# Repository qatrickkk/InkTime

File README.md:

# InkTime Smartwatch

InkTime is a custom, open source smartwatch based on Nordic nRF52840, designed to have a low power consumption. It features an E-Ink display, 3-axis accelerometer, haptic feedback, and a 3 button navigation system.

## System Architecture Diagram
```mermaid
flowchart LR
    subgraph PWR["Power Subsystem"]
        USB["USB-C"]
        CHG["BQ25180<br/>Li-Ion Charger / Power Path"]
        BAT["AKY0106<br/>Li-Po Battery"]
        FG["MAX17048<br/>Fuel Gauge"]
        REG["RT6160<br/>Buck-Boost 3.3 V"]
        EPDPWR["E-Paper Drive Circuit<br/>(boost / gate / HV rails)"]
    end

    subgraph CTRL["Main Control"]
        MCU["nRF52840"]
    end

    subgraph PERI["Peripherals"]
        EPD["WSH-12561<br/>E-Ink Display"]
        IMU["BMA423 IMU"]
        HAPTIC["DRV2605<br/>Haptic Driver"]
        MOTOR["FIT0774<br/>Vibration Motor"]
        BTN["3 Physical Buttons<br/>(UP / ENTER / DOWN)"]
    end

    USB -->|VBUS| CHG
    BAT <-->|VBAT| CHG
    BAT -->|Cell voltage| FG
    CHG -->|SYS / VREG| REG
    REG -->|3V3| MCU
    REG -->|3V3| IMU
    REG -->|3V3| FG
    REG -->|3V3| HAPTIC
    REG -->|3V3| EPDPWR
    EPDPWR -->|EPD_3V3 + PREVGH / PREVGL| EPD

    MCU <-->|I2C| IMU
    MCU <-->|I2C| FG
    MCU <-->|I2C| HAPTIC
    MCU <-->|I2C| CHG
    MCU <-->|I2C| REG

    MCU -->|SPI SCK / MOSI| EPD
    MCU -->|GPIO: CS / DC / RST| EPD
    EPD -->|GPIO: BUSY| MCU

    MCU <-->|GPIO| BTN
    MCU -->|EN / TRIG| HAPTIC
    HAPTIC -->|OUT+ / OUT-| MOTOR
```

## Hardware Functionality
The nRF52840 is the central controller of the InkTime smartwatch. It runs the firmware, decides when to sleep and wake up, reads sensors, updates the display, handles the buttons, and manages communication with the other chips.

Around the MCU, there are five smaller systems that work together to create a fully functional smartwatch.

The power system is responsible for providing clean power used to charge and operate the watch.

- USB-C brings power from the charger,
- BQ25180 charges the battery and manages the power flow,
- AKY0106 is the battery itself,
- RT6160 generates the regulated 3.3 V rail,
- MAX17048 monitors the battery status and indicates how full it is.

The display system is the bridge between the internal data and the actual information the user sees. Unlike LCD or OLED panels, it does not need continuous power to hold an image, because the ink particles remain in the same position. Therefore, power is mainly used only when the image is changed or refreshed, making it well suited for this use case.

The motion system helps the smartwatch stay in a low-power state by using IMU data, allowing the watch to wake up only when a specific motion occurs, for example a tilt.

The haptic system is based on the DRV2605 haptic driver. Its role is to give the smartwatch user physical feedback through vibration, for example when a notification appears, an alarm is triggered, or a button press is confirmed.

The user input system is formed by three physical buttons: SW_UP, SW_ENT, and SW_DW. These buttons allow the user to interact with the smartwatch in a simple and reliable way.

Power Profile Estimate
- the nRF52840 stays in deep sleep most of the time, below 10 µA,
- the watch wakes once per minute,
- the E-Ink display is refreshed for about 1–2 s,
- active current during refresh is around 8–10 mA.

## nRF52840 Pin Allocation
| Peripheral       | Pin(s)        | Function     | Justification                                 |
| ---------------- | ------------- | ------------ | --------------------------------------------- |
| SPI SCK          | P0.02         | Clock        | SPI clock for the E-Ink display.              |
| SPI MOSI         | P0.03         | Data         | Sends pixel data to the E-Ink display.        |
| EPD CS           | P0.05         | Chip Select  | Selects the display on the SPI bus.           |
| I2C SDA          | P0.06         | Data         | Shared data line for sensors and power ICs.   |
| I2C SCL          | P0.07         | Clock        | Shared clock line for the I2C bus.            |
| IMU INT1         | P0.08         | Interrupt    | Main interrupt from the IMU.                  |
| Fuel Gauge ALERT | P0.09         | Interrupt    | Battery alert signal from MAX17048.           |
| PMIC INT         | P0.11         | Interrupt    | Status or fault signal from BQ25180.          |
| HAPTIC_EN        | P0.12         | Control      | Controls the haptic driver.                   |
| Button UP        | P0.13         | GPIO Input   | Reads the UP button state.                    |
| Button ENTER     | P0.14         | GPIO Input   | Reads the ENTER button state.                 |
| EPD DC           | P0.15         | Control      | Selects command or data mode for the display. |
| EPD RST          | P0.16         | Control      | Resets the E-Ink display.                     |
| EPD BUSY         | P0.17         | Status Input | Shows when the display is busy refreshing.    |
| nRESET           | P0.18 / RESET | Reset        | Resets the MCU.                               |
| Button DOWN      | P1.02         | GPIO Input   | Reads the DOWN button state.                  |
| IMU INT2         | P1.08         | Interrupt    | Secondary interrupt from the IMU.             |
| USB D+           | D+            | USB Data     | USB communication line.                       |
| USB D-           | D-            | USB Data     | USB communication line.                       |
| SWDIO            | SWDIO         | Debug        | Debug and programming data line.              |
| SWDCLK           | SWDCLK        | Debug        | Debug and programming clock line.             |

## Bill of Materials (BOM)
| Qty | Value             | Parts                                                                     | Device                              | Package                      | Product Link                                                                        | Datasheet Link                                                                                                                                   |
| --: | ----------------- | ------------------------------------------------------------------------- | ----------------------------------- | ---------------------------- | ----------------------------------------------------------------------------------- | ------------------------------------------------------------------------------------------------------------------------------------------------ |
|   1 | nRF52840-QIAA     | U1                                                                        | NORDIC_NRF_4_NRF52840_QF            | AQFN-73-EP(7x7)              | [JLCPCB](https://jlcpcb.com/partdetail/NordicSemicon-NRF52840_QIAAR/C190794)        | [Datasheet](https://infocenter.nordicsemi.com/pdf/nRF52840_PS_v1.9.pdf)                                                                          |
|   1 | BQ25180YBGR       | IC1                                                                       | BQ25180YBGR                         | DSBGA-8(1.1x1.6)             | [JLCPCB](https://jlcpcb.com/partdetail/TexasInstruments-BQ25180YBGR/C3682423)       | [Datasheet](https://www.ti.com/lit/ds/symlink/bq25180.pdf)                                                                                       |
|   1 | MAX17048G+T10     | U3                                                                        | ESP32_C6_LIBRARY_MAX17048G+T10      | DFN-8-EP(2x2)                | [JLCPCB](https://jlcpcb.com/partdetail/MaximIntegrated-MAX17048GT10/C2682616)       | [Datasheet](https://www.analog.com/media/en/technical-documentation/data-sheets/MAX17048-MAX17049.pdf)                                           |
|   1 | DRV2605YZFR       | IC2                                                                       | DRV2605YZFR                         | DSBGA-9                      | [JLCPCB](https://jlcpcb.com/partdetail/TexasInstruments-DRV2605YZFR/C81079)         | [Datasheet](https://www.ti.com/lit/ds/symlink/drv2605.pdf)                                                                                       |
|   1 | DMG2305UX-7       | P-channel MOSFET                                                          | DMG2305UX-7                         | SOT-23                       | [JLCPCB](https://jlcpcb.com/partdetail/HXYMOSFET-DMG2305UX7/C5261054)               | [Datasheet](https://www.diodes.com/assets/Datasheets/DMG2305UX.pdf)                                                                              |
|   1 | SI1308EDL-T1-GE3  | Q3                                                                        | ESP32_C6_LIBRARY_6_SI1308EDL-T1-GE3 | SOT-323                      | [JLCPCB](https://jlcpcb.com/partdetail/TECHPUBLIC-SI1308EDL/C7603347)               | [Datasheet](https://www.vishay.com/docs/63399/si1308edl.pdf)                                                                                     |
|   3 | MBR0530           | D2, D4, D5                                                                | MBR0530                             | SOD-123                      | [JLCPCB](https://jlcpcb.com/partdetail/4324765-MBR0530_F20000HF/C3757235)           | [Datasheet](https://wmsc.lcsc.com/wmsc/upload/file/pdf/v2/lcsc/2205311800_Yangzhou-Yangjie-Electronic-Technology-MBR0530-F2-0000HF_C3757235.pdf) |
|   1 | USBLC6-2SC6Y      | D3                                                                        | USBLC6-2SC6Y                        | SOT-23-6                     | [JLCPCB](https://jlcpcb.com/partdetail/TECHPUBLIC-USBLC62SC6Y/C5310974)             | [Datasheet](https://wmsc.lcsc.com/wmsc/upload/file/pdf/v2/lcsc/2401261525_TECH-PUBLIC-USBLC6-2SC6Y_C5310974.pdf)                                 |
|   1 | 2450AT18B100E     | ANT1                                                                      | 2450AT18B100E_2450AT18B100E         | ANTC3216X140N / 1206 class   | [JLCPCB](https://jlcpcb.com/partdetail/JohansonTechnology-2450AT18B100/C2836414)    | [Datasheet](https://www.johansontechnology.com/datasheets/antennas/2450AT18B100.pdf)                                                             |
|   1 | KH-TYPE-C-16P     | J4                                                                        | KH-TYPE-C-16P_KH-TYPE-C-16P         | SMD                          | [JLCPCB](https://jlcpcb.com/partdetail/KH-TYPE-C-16P/C709357)                       | [Datasheet](https://wmsc.lcsc.com/wmsc/upload/file/pdf/v2/lcsc/2204251630_SHENZHEN-KINGHELM-Elec-KH-TYPE-C-16P_C709357.pdf)                      |
|   3 | EVP-AKE31A        | SW_DN, SW_ENT, SW_UP                                                      | EVP-AKE31A                          | SW_EVP-AKE31A_PAN            | [JLCPCB](https://jlcpcb.com/partdetail/PANASONIC-EVPAKE31A/C569760)                 | [Datasheet](https://www.lcsc.com/datasheet/C569760.pdf)                                                                                          |
|   1 | FTC252012SR47MBCA | L7                                                                        | MLP2016SR47MT0S1_FTC252012SR47MBCA  | INDC2016X100N                | [JLCPCB](https://jlcpcb.com/partdetail/6763488-FTC252012SR47MBCA/C5832368)          | [Datasheet](https://wmsc.lcsc.com/wmsc/upload/file/pdf/v2/lcsc/2311271530_TDK-FTC252012SR47MBCA_C5832368.pdf)                                    |
|   1 | 32.768 kHz        | X2                                                                        | NORDIC_NRF_1_XTAL_32KHZ             | SMD3215-2P                   | [JLCPCB](https://jlcpcb.com/partdetail/NDK-NX3215SA_32_768K_STD_MUA9/C519280)       | [Datasheet](https://www.ndk.com/images/products/crystal/resonator/NX3215SA_e.pdf)                                                                |
|   6 | 10K               | R2_EP_DR, R5, R7, R8, R9, R_PWR_EPD                                       | RC0201FR-1310KL                     | 0201                         | [JLCPCB](https://jlcpcb.com/partdetail/YAGEO-RC0201FR1310KL/C6373588)               | [Datasheet](https://www.lcsc.com/datasheet/C6373588.pdf)                                                                                         |
|   2 | 5K1               | R1_USB, R2_USB                                                            | RC0201FR-075K1L                     | 0201                         | [JLCPCB](https://jlcpcb.com/partdetail/YAGEO-RC0201FR075K1L/C274341)                | [Datasheet](https://www.lcsc.com/datasheet/C274341.pdf)                                                                                          |
|   2 | 3K3               | R17, R18                                                                  | RNCF0201DTC3K30                     | 0201                         | [JLCPCB](https://jlcpcb.com/partdetail/SEI_Stackpole_Elec-RNCF0201DTC3K30/C2487997) | [Datasheet](https://www.lcsc.com/datasheet/C2487997.pdf)                                                                                         |
|   3 | 0R                | R2, R3, R4                                                                | 0201WMJ0000TCE                      | 0201                         | [JLCPCB](https://jlcpcb.com/partdetail/25793-0201WMJ0000TCE/C25050)                 | [Datasheet](https://www.lcsc.com/datasheet/C25050.pdf)                                                                                           |
|   1 | 2.2Ω              | R_TYPE_SEL                                                                | 0201WMF220KTCE                      | 0201                         | [JLCPCB](https://jlcpcb.com/partdetail/244650-0201WMF220KTCE/C247442)               | [Datasheet](https://www.lcsc.com/datasheet/C247442.pdf)                                                                                          |
|   9 | 100nF             | C5, C7, C8, C12, C19, C23, C27, C34, C42                                  | AC0201KRX6S6BB104                   | 0201                         | [JLCPCB](https://jlcpcb.com/partdetail/YAGEO-AC0201KRX6S6BB104/C3855913)            | [Datasheet](https://www.lcsc.com/datasheet/C3855913.pdf)                                                                                         |
|   4 | 12pF              | C1, C2, C17, C18                                                          | 0201N120J250CT                      | 0201                         | [JLCPCB](https://jlcpcb.com/partdetail/Walsin_TechCorp-0201N120J250CT/C424835)      | [Datasheet](https://www.lcsc.com/datasheet/C424835.pdf)                                                                                          |
|   2 | 1pF               | C3, C4                                                                    | GRM0335C1E1R0CA01J                  | 0201                         | [JLCPCB](https://jlcpcb.com/partdetail/2274979-GRM0335C1E1R0CA01J/C2182912)         | [Datasheet](https://www.lcsc.com/datasheet/C2182912.pdf)                                                                                         |
|   1 | 100pF             | C11                                                                       | 0201N101F160CT                      | 0201                         | [JLCPCB](https://jlcpcb.com/partdetail/Walsin_TechCorp-0201N101F160CT/C3847857)     | [Datasheet](https://www.lcsc.com/datasheet/C3847857.pdf)                                                                                         |
|   1 | 47nF              | C16                                                                       | C0201X5R473K160NTA                  | 0201                         | [JLCPCB](https://jlcpcb.com/partdetail/126083-C0201X5R473K160NTA/C124806)           | [Datasheet](https://www.lcsc.com/datasheet/C124806.pdf)                                                                                          |
|   1 | 1uF               | C15                                                                       | CL05A105KP5NNNC                     | 0402                         | [JLCPCB](https://jlcpcb.com/partdetail/C14445)                                      | [Datasheet](https://www.lcsc.com/datasheet/C14445.pdf)                                                                                           |
|   5 | 4.7uF             | C6, C14, C20, C21, C43                                                    | GRM155R61A475KEAAD                  | 0402                         | [JLCPCB](https://jlcpcb.com/partdetail/MurataElectronics-GRM155R61A475KEAAD/C77004) | [Datasheet](https://www.lcsc.com/datasheet/C77004.pdf)                                                                                           |
|   1 | 4.7uF / 25V       | C2-EP-DR                                                                  | C0402X5R475M250NT                   | 0402                         | [JLCPCB](https://jlcpcb.com/partdetail/SANYEAR-C0402X5R475M250NT/C2911388)          | [Datasheet](https://www.lcsc.com/datasheet/C2911388.pdf)                                                                                         |
|   9 | 1uF / 50V         | EPD_C1, EPD_C2, EPD_C6, EPD_C7, EPD_C8, EPD_C9, EPD_C10, EPD_C11, EPD_C12 | GRM155R61H105KE05D                  | 0402                         | [JLCPCB](https://jlcpcb.com/partdetail/1609005-GRM155R61H105KE05D/C1518208)         | [Datasheet](https://www.lcsc.com/datasheet/C1518208.pdf)                                                                                         |
|   2 | 10uF              | C24, C39                                                                  | 0402X106M100CT                      | 0402                         | [JLCPCB](https://jlcpcb.com/partdetail/Walsin_TechCorp-0402X106M100CT/C2992625)     | [Datasheet](https://www.lcsc.com/datasheet/C2992625.pdf)                                                                                         |
|   2 | 22uF              | C25, C33                                                                  | CL05A226MQ6ZUN8                     | 0402                         | [JLCPCB](https://jlcpcb.com/partdetail/2889851-CL05A226MQ6ZUN8/C2762589)            | [Datasheet](https://www.lcsc.com/datasheet/C2762589.pdf)                                                                                         |
|   1 | 820pF             | C9                                                                        | MA0201XF821K250                     | 0201                         | [JLCPCB](https://jlcpcb.com/partdetail/Meritek-MA0201XF821K250/C3842403)            | [Datasheet](https://www.lcsc.com/datasheet/C3842403.pdf)                                                                                         |
|   1 | 32MHz             | X1                                                                        | NX2016SA-32MHZ-STD-CZS-5            | SMD2016-4P                   | [JLCPCB](https://jlcpcb.com/partdetail/NDK-NX2016SA_32MHZ_STD_CZS5/C843260)         | [Datasheet](https://www.lcsc.com/datasheet/C843260.pdf)                                                                                          |
|   1 | 3.9nH             | L1                                                                        | VHF060303H3N9ST                     | 0201                         | [JLCPCB](https://jlcpcb.com/partdetail/153834-VHF060303H3N9ST/C142503)              | [Datasheet](https://www.lcsc.com/datasheet/C142503.pdf)                                                                                          |
|   1 | 15nH              | L3                                                                        | MLK0603L15NJT000                    | 0201                         | [JLCPCB](https://jlcpcb.com/partdetail/TDK-MLK0603L15NJT000/C6990407)               | [Datasheet](https://www.lcsc.com/datasheet/C6990407.pdf)                                                                                         |
|   1 | BMA421            | IC3                                                                       | BMA421                              | LGA-12(2x2)                  | [JLCPCB](https://jlcpcb.com/partdetail/BoschSensortec-BMA421/C5242966)              | [Datasheet](https://files.pine64.org/doc/datasheet/pinetime/BST-BMA421-FL000.pdf)                                                                |
|   1 | RT6160AWSC        | IC9                                                                       | RT6160AWSC                          | WLCSP-15B(2.3x1.4)           | [JLCPCB](https://jlcpcb.com/partdetail/RichtekTech-RT6160AWSC/C7065276)             | [Datasheet](https://www.mouser.com/datasheet/2/1458/DS6160A_03-3104604.pdf)                                                                      |
|   1 | 503480-2400       | J1                                                                        | 5034802400                          | 24-pin 0.5mm right-angle FPC | [JLCPCB](https://jlcpcb.com/partdetail/MOLEX-5034802400/C122434)                    | [Datasheet](https://www.mouser.com/datasheet/2/276/2/5034802400_FFC_FPC_CONNECTORS-1112921.pdf)                                                  |

## Mechanical Design Log
The following design decisions were made during the hardware development process in order to meet the mechanical and electrical constraints of the project:

* **Board thickness:** The PCB was designed with a thickness of **1 mm** to match the enclosure dimensions. All components were placed on the **TOP layer**.
* **Antenna design:** The antenna was placed on the outer edge of the PCB. The area below the antenna was kept free of traces and ground copper to preserve RF performance. Via stitching was also added between the ground planes around the radio section.
* **Routing rules:** Power traces were routed with a width of **0.3 mm**, while data traces were routed with a minimum width of **0.15 mm**. The **100 nF decoupling capacitors** were placed as close as possible to the power pins of the ICs. For some BGA devices and for the MCU, **0.15 mm power traces** were also used locally to allow proper fanout from the pins.
* **Enclosure adjustments:** The case was modified by a few millimeters where needed so that all parts could fit correctly and to avoid overlap errors. The main changes were made to provide enough clearance for the **display** and the **battery** inside the enclosure.
* **BGA / MCU vias:** For BGA-type components and for the MCU, **via-in-pad style escape routing** was used in some areas, with **0.15 mm / 0.2 mm** via dimensions, as allowed by the course requirements.
* **Accepted errors:** The DRC **“Dimension”** errors related to the three buttons and the USB connector were intentionally accepted, since their placement was dictated by the mechanical alignment with the enclosure cutouts. The **“Only INPUT pins on NET ID”** error was also ignored, since it is an accepted behavior in this project context.

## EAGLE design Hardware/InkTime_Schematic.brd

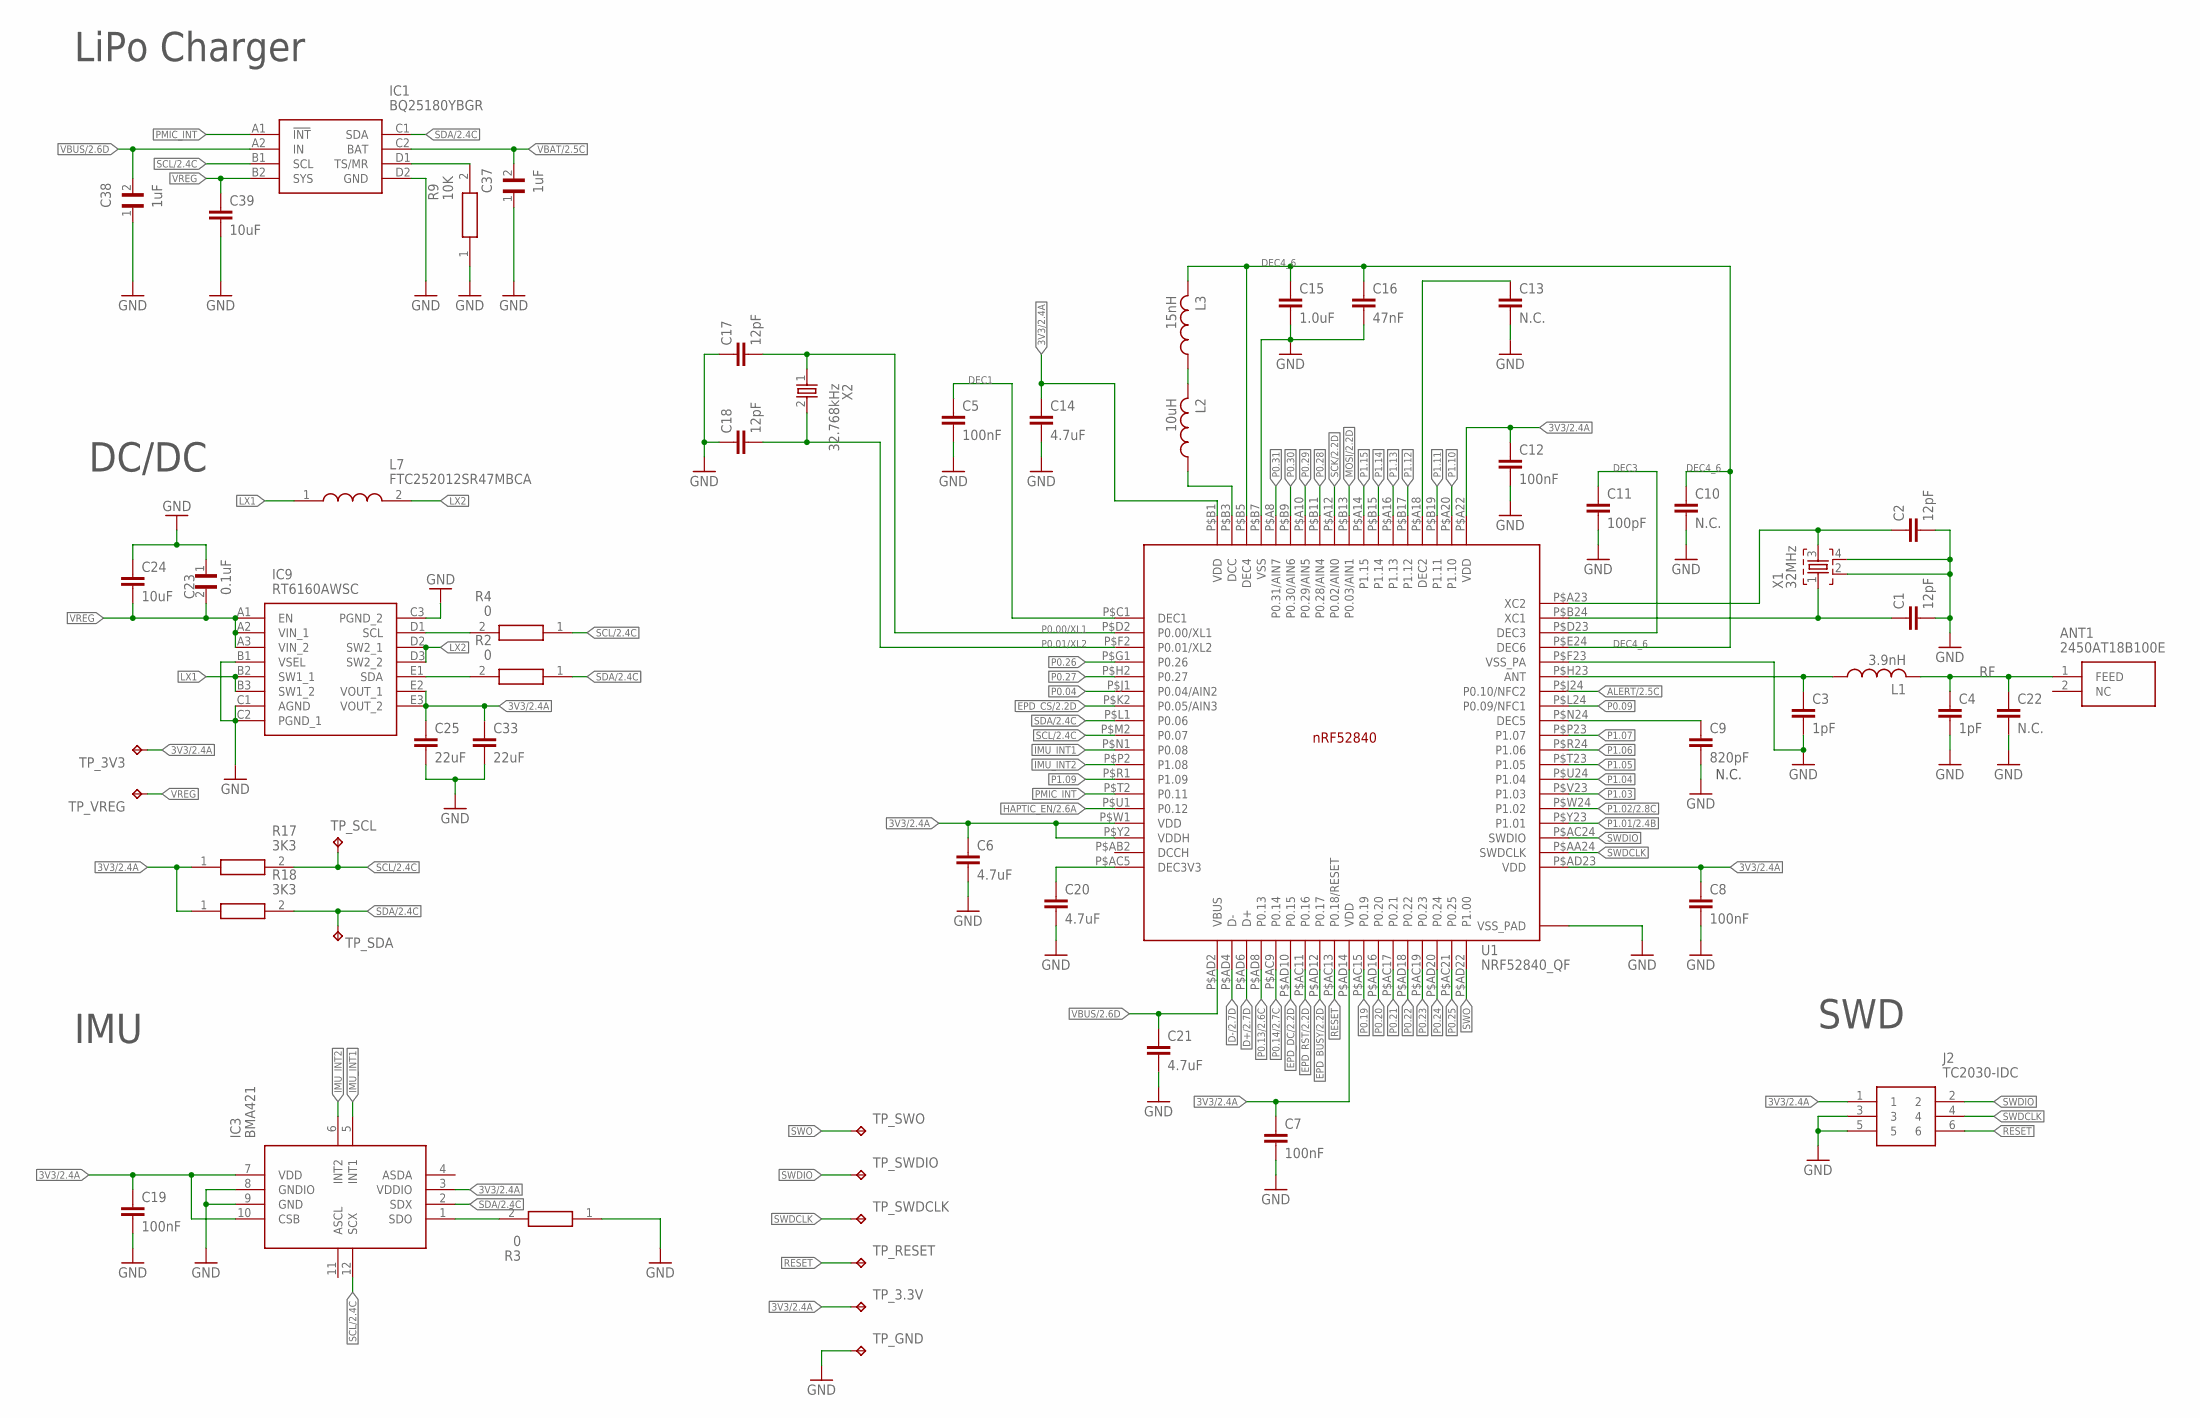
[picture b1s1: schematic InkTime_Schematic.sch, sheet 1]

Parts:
ANT1: 2450AT18B100E; 2450AT18B100E_ANTC3216X140N
C1, C2, C17, C18: 12pF; GRM011R60J152KE01L_2_CAPC0201X13N
C3, C4: 1pF; GRM011R60J152KE01L_2_CAPC0201X13N
C5, C7, C8, C12, C19: 100nF; GRM011R60J152KE01L_2_CAPC0201X13N
C6, C14, C20, C21: 4.7uF; NORDIC_NRF_3_RESC0402_L
C9: 820pF; GRM011R60J152KE01L_2_CAPC0201X13N
C10, C13, C22: N.C.; GRM011R60J152KE01L_2_CAPC0201X13N
C11: 100pF; GRM011R60J152KE01L_2_CAPC0201X13N
C15: 1.0uF; NORDIC_NRF_3_RESC0402_L
C16: 47nF; GRM011R60J152KE01L_2_CAPC0201X13N
C23: 0.1uF; GRM011R60J152KE01L_2_CAPC0201X13N
C24, C39: 10uF; NORDIC_NRF_3_RESC0402_L
C25, C33: 22uF; NORDIC_NRF_3_RESC0402_L
C37, C38: 1uF; GRM011R60J152KE01L_2_CAPC0201X13N
IC1: BQ25180YBGR; BQ25180YBGR_BGA8C40P2X4_100X155X50
IC3: BMA421; BMA423_BMA423
IC9: RT6160AWSC; RT6160AWSC_BGA15C40P3X5_140X230X60
J2: TC2030-IDC; TC2030-IDC_TC2030IDC
L1: 3.9nH; NORDIC_NRF_2_RESC0201_L
L2: 10uH; NORDIC_NRF_2_RESC0201_L
L3: 15nH; NORDIC_NRF_2_RESC0201_L
L7: FTC252012SR47MBCA; MLP2016SR47MT0S1_INDC2016X100N
R2, R3, R4: 0; CPF0201D7K68C1_0201
R9: 10K; CPF0201D7K68C1_0201
R17, R18: 3K3; CPF0201D7K68C1_0201
TP_3.3V, TP_3V3: HECTOR_WATCH_1_TPTP20R; HECTOR_WATCH_1_TP20R
TP_GND: HECTOR_WATCH_1_TPTP20R; HECTOR_WATCH_1_TP20R
TP_RESET: HECTOR_WATCH_1_TPTP20R; HECTOR_WATCH_1_TP20R
TP_SCL: HECTOR_WATCH_1_TPTP20R; HECTOR_WATCH_1_TP20R
TP_SDA: HECTOR_WATCH_1_TPTP20R; HECTOR_WATCH_1_TP20R
TP_SWDCLK: HECTOR_WATCH_1_TPTP20R; HECTOR_WATCH_1_TP20R
TP_SWDIO: HECTOR_WATCH_1_TPTP20R; HECTOR_WATCH_1_TP20R
TP_SWO: HECTOR_WATCH_1_TPTP20R; HECTOR_WATCH_1_TP20R
TP_VREG: HECTOR_WATCH_1_TPTP20R; HECTOR_WATCH_1_TP20R
U1: NRF52840_QF; NORDIC_NRF_4_AQFN50P700X700X85_HS-74N
X1: 32MHz; NORDIC_NRF_BT-XTAL_2016_N
X2: 32.768kHz; NORDIC_NRF_1_XTAL_3215_N

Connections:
3V3/2.4A: C6.1, C7.1, C8.1, C12.1, C14.1, C19.1, C25.1, C33.1, IC3.3 (VDDIO), IC3.7 (VDD), IC3.10 (CSB), IC9.E2 (VOUT_1), IC9.E3 (VOUT_2), J2.1, R17.1, R18.1, TP_3.3V.TP, TP_3V3.TP, U1.P$A22 (VDD), U1.P$AD14 (VDD), U1.P$AD23 (VDD), U1.P$B1 (VDD), U1.P$W1 (VDD), U1.P$Y2 (VDDH)
ALERT/2.5C: U1.P$J24 (P0.10/NFC2)
D+/2.7D: U1.P$AD6 (D+)
D-/2.7D: U1.P$AD4 (D-)
DEC1: C5.1, U1.P$C1 (DEC1)
DEC3: C11.1, U1.P$D23 (DEC3)
DEC4_6: C10.1, C15.1, C16.1, L3.2, U1.P$B5 (DEC4), U1.P$E24 (DEC6)
EPD_BUSY/2.2D: U1.P$AD12 (P0.17)
EPD_CS/2.2D: U1.P$K2 (P0.05/AIN3)
EPD_DC/2.2D: U1.P$AD10 (P0.15)
EPD_RST/2.2D: U1.P$AC11 (P0.16)
GND: C1.2, C2.2, C3.2, C4.2, C5.2, C6.2, C7.2, C8.2, C9.2, C10.2, C11.2, C12.2, C13.2, C14.2, C15.2, C16.2, C17.1, C18.1, C19.2, C20.2, C21.2, C22.2, C23.1, C24.1, C25.2, C33.2, C37.1, C38.1, C39.2, IC1.D2 (GND), IC3.8 (GNDIO), IC3.9 (GND), IC9.B1 (VSEL), IC9.C1 (AGND), IC9.C2 (PGND_1), IC9.C3 (PGND_2), J2.3, J2.5, R3.1, R9.1, TP_GND.TP, U1.P$74 (VSS_PAD), U1.P$75 (VSS_PAD), U1.P$76 (VSS_PAD), U1.P$77 (VSS_PAD), U1.P$78 (VSS_PAD), U1.P$79 (VSS_PAD), U1.P$80 (VSS_PAD), U1.P$81 (VSS_PAD), U1.P$82 (VSS_PAD), U1.P$83 (VSS_PAD), U1.P$84 (VSS_PAD), U1.P$85 (VSS_PAD), U1.P$86 (VSS_PAD), U1.P$87 (VSS_PAD), U1.P$88 (VSS_PAD), U1.P$89 (VSS_PAD), U1.P$90 (VSS_PAD), U1.P$B7 (VSS), U1.P$F23 (VSS_PA), X1.2, X1.4; also elsewhere on the board
HAPTIC_EN/2.6A: U1.P$U1 (P0.12)
IMU_INT1: IC3.5 (INT1), U1.P$N1 (P0.08)
IMU_INT2: IC3.6 (INT2), U1.P$P2 (P1.08)
LX1: IC9.B2 (SW1_1), IC9.B3 (SW1_2), L7.1
LX2: IC9.D2 (SW2_1), IC9.D3 (SW2_2), L7.2
MOSI/2.2D: U1.P$B13 (P0.03/AIN1)
unnamed: IC1.D1 (TS/MR), R9.2
unnamed: C2.1, U1.P$A23 (XC2), X1.3
unnamed: C1.1, U1.P$B24 (XC1), X1.1
unnamed: C3.1, L1.1, U1.P$H23 (ANT)
unnamed: IC3.1 (SDO), R3.2
unnamed: IC9.E1 (SDA), R2.2
unnamed: C9.1, U1.P$N24 (DEC5)
unnamed: IC9.D1 (SCL), R4.2
unnamed: L2.1, U1.P$B3 (DCC)
unnamed: L2.2, L3.1
unnamed: C13.1, U1.P$A18 (DEC2)
unnamed: C20.1, U1.P$AC5 (DEC3V3)
P0.00/XL1: C17.2, U1.P$D2 (P0.00/XL1), X2.1
P0.01/XL2: C18.2, U1.P$F2 (P0.01/XL2), X2.2
P0.04: U1.P$J1 (P0.04/AIN2)
P0.09: U1.P$L24 (P0.09/NFC1)
P0.13/2.6C: U1.P$AD8 (P0.13)
P0.14/2.7C: U1.P$AC9 (P0.14)
P0.19: U1.P$AC15 (P0.19)
P0.20: U1.P$AD16 (P0.20)
P0.21: U1.P$AC17 (P0.21)
P0.22: U1.P$AD18 (P0.22)
P0.23: U1.P$AC19 (P0.23)
P0.24: U1.P$AD20 (P0.24)
P0.25: U1.P$AC21 (P0.25)
P0.26: U1.P$G1 (P0.26)
P0.27: U1.P$H2 (P0.27)
P0.28: U1.P$B11 (P0.28/AIN4)
P0.29: U1.P$A10 (P0.29/AIN5)
P0.30: U1.P$B9 (P0.30/AIN6)
P0.31: U1.P$A8 (P0.31/AIN7)
P1.01/2.4B: U1.P$Y23 (P1.01)
P1.02/2.8C: U1.P$W24 (P1.02)
P1.03: U1.P$V23 (P1.03)
P1.04: U1.P$U24 (P1.04)
P1.05: U1.P$T23 (P1.05)
P1.06: U1.P$R24 (P1.06)
P1.07: U1.P$P23 (P1.07)
P1.09: U1.P$R1 (P1.09)
P1.10: U1.P$A20 (P1.10)
P1.11: U1.P$B19 (P1.11)
P1.12: U1.P$B17 (P1.12)
P1.13: U1.P$A16 (P1.13)
P1.14: U1.P$B15 (P1.14)
P1.15: U1.P$A14 (P1.15)
PMIC_INT: IC1.A1 (!INT), U1.P$T2 (P0.11)
RESET: J2.6, TP_RESET.TP, U1.P$AC13 (P0.18/RESET)
RF: ANT1.1 (FEED), C4.1, C22.1, L1.2
SCK/2.2D: U1.P$A12 (P0.02/AIN0)
SCL/2.4C: IC1.B1 (SCL), IC3.12 (SCX), R4.1, R17.2, TP_SCL.TP, U1.P$M2 (P0.07)
SDA/2.4C: IC1.C1 (SDA), IC3.2 (SDX), R2.1, R18.2, TP_SDA.TP, U1.P$L1 (P0.06)
SWDCLK: J2.4, TP_SWDCLK.TP, U1.P$AA24 (SWDCLK)
SWDIO: J2.2, TP_SWDIO.TP, U1.P$AC24 (SWDIO)
SWO: TP_SWO.TP, U1.P$AD22 (P1.00)
VBAT/2.5C: C37.2, IC1.C2 (BAT)
VBUS/2.6D: C21.1, C38.2, IC1.A2 (IN), U1.P$AD2 (VBUS)
VREG: C23.2, C24.2, C39.1, IC1.B2 (SYS), IC9.A1 (EN), IC9.A2 (VIN_1), IC9.A3 (VIN_2), TP_VREG.TP

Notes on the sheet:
LiPo Charger
DC/DC
IMU
SWD
N.C.

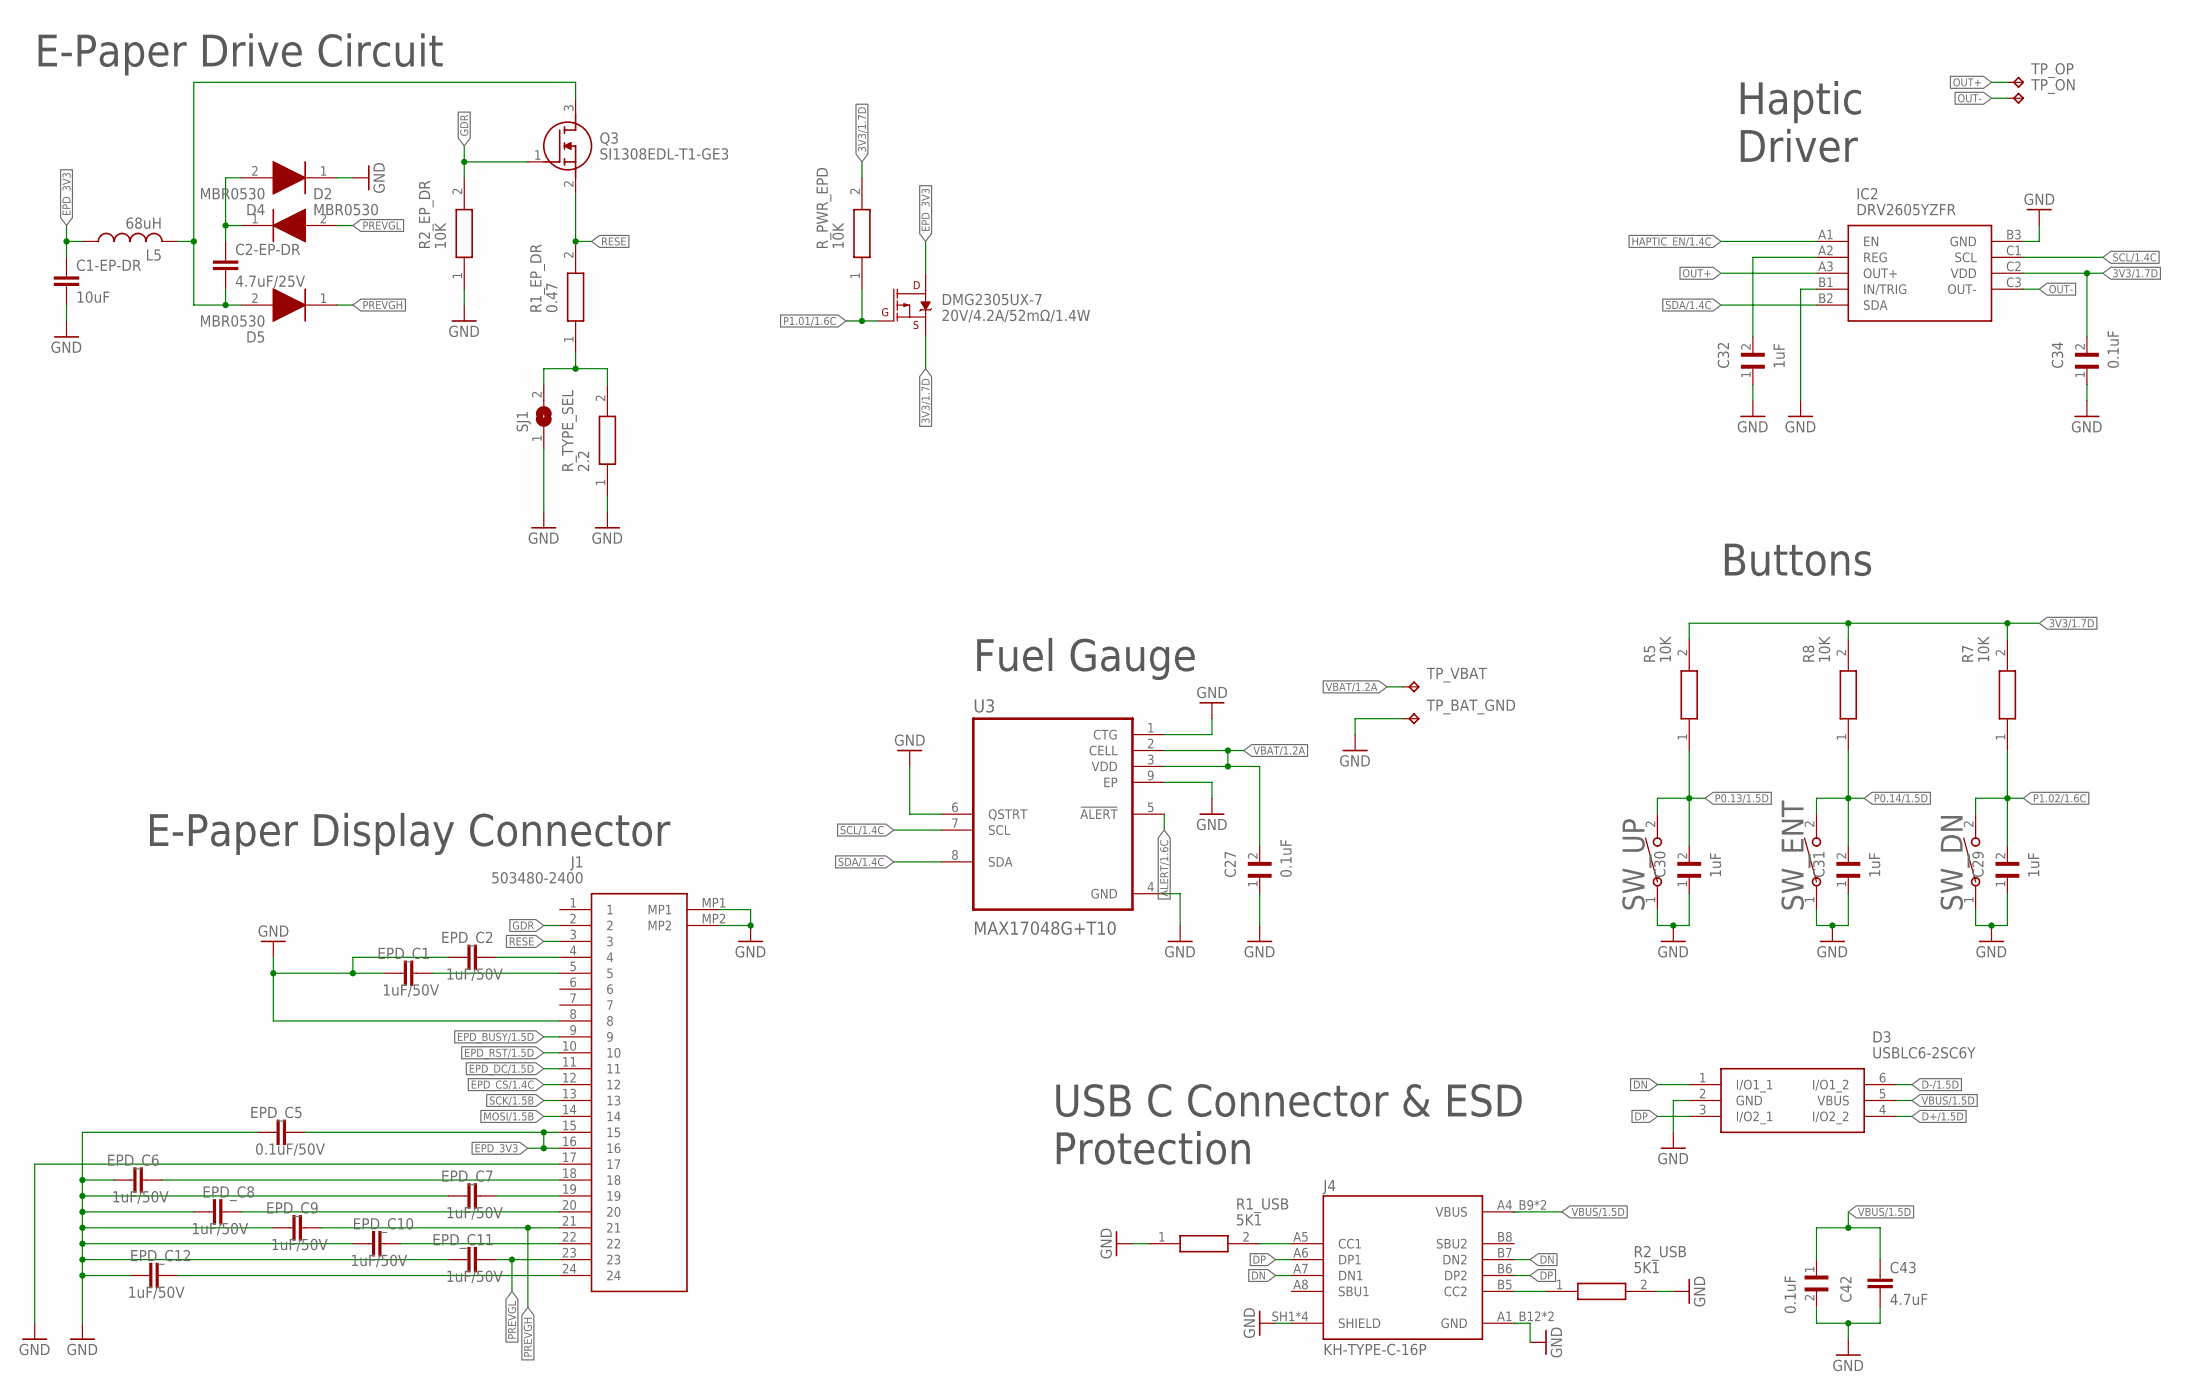
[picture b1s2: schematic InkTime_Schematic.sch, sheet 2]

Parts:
C1-EP-DR: 10uF; GRM011R60J152KE01L_2_CAPC0201X13N
C2-EP-DR: 4.7uF/25V; NORDIC_NRF_3_RESC0402_L
C27, C34, C42: 0.1uF; GRM011R60J152KE01L_2_CAPC0201X13N
C29, C30, C31, C32: 1uF; GRM011R60J152KE01L_2_CAPC0201X13N
C43: 4.7uF; NORDIC_NRF_3_RESC0402_L
D2, D4, D5: MBR0530; ESP32_C6_LIBRARY_5_SOD3716X135N
D3: USBLC6-2SC6Y; ESP32_C6_LIBRARY_3_SOT95P280X145-6N
DMG2305UX-7: 20V/4.2A/52mΩ/1.4W; ESP32_C6_LIBRARY_4_ESP32_C6_LIBRARY_4_ESP32_C6_LIBRARY_4_ES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
EPD_C1, EPD_C2, EPD_C6, EPD_C7, EPD_C8, EPD_C9, EPD_C10, EPD_C11, EPD_C12: 1uF/50V; NORDIC_NRF_3_RESC0402_L
EPD_C5: 0.1uF/50V; GRM011R60J152KE01L_2_CAPC0201X13N
IC2: DRV2605YZFR; DRV2605YZFR_BGA9C50P3X3_144X144X62
J1: 503480-2400; 503480-2400_5034802400
J4: KH-TYPE-C-16P; KH-TYPE-C-16P_KINGHELM_KH-TYPE-C-16P
L5: 68uH; NORDIC_NRF_2_RESC0201_L
Q3: SI1308EDL-T1-GE3; ESP32_C6_LIBRARY_6_SOT65P210X110-3N
R1_EP_DR: 0.47; CPF0201D7K68C1_0201
R1_USB, R2_USB: 5K1; CPF0201D7K68C1_0201
R2_EP_DR, R5, R7, R8: 10K; CPF0201D7K68C1_0201
R_PWR_EPD: 10K; CPF0201D7K68C1_0201
R_TYPE_SEL: 2.2; CPF0201D7K68C1_0201
SJ1: ESP32_C6_LIBRARY_7_JUMPER_SJ
SW_DN: 2025-10-22_07-23-44_LIBRARY_EVP-AKE31ASW_EVP-AKE3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; 2025-10-22_07-23-44_LIBRARY_SW_EVP-AKE31A_PAN
SW_ENT: 2025-10-22_07-23-44_LIBRARY_EVP-AKE31ASW_EVP-AKE3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; 2025-10-22_07-23-44_LIBRARY_SW_EVP-AKE31A_PAN
SW_UP: 2025-10-22_07-23-44_LIBRARY_EVP-AKE31ASW_EVP-AKE3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; 2025-10-22_07-23-44_LIBRARY_SW_EVP-AKE31A_PAN
TP_BAT_GND: HECTOR_WATCH_1_TPTP20R; HECTOR_WATCH_1_TP20R
TP_ON: HECTOR_WATCH_1_TPTP20R; HECTOR_WATCH_1_TP20R
TP_OP: HECTOR_WATCH_1_TPTP20R; HECTOR_WATCH_1_TP20R
TP_VBAT: HECTOR_WATCH_1_TPTP20R; HECTOR_WATCH_1_TP20R
U3: MAX17048G+T10; ESP32_C6_LIBRARY_SON50P200X200X80-9N

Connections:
3V3/1.7D: C34.2, DMG2305UX-7.2 (S), IC2.C2 (VDD), R5.2, R7.2, R8.2, R_PWR_EPD.2
ALERT/1.6C: U3.5 (!ALERT)
D+/1.5D: D3.4 (I/O2_2)
D-/1.5D: D3.6 (I/O1_2)
DN: D3.1 (I/O1_1), J4.A7 (DN1), J4.B7 (DN2)
DP: D3.3 (I/O2_1), J4.A6 (DP1), J4.B6 (DP2)
EPD_3V3: C1-EP-DR.1, DMG2305UX-7.3 (D), EPD_C5.2, J1.15, J1.16, L5.1
EPD_BUSY/1.5D: J1.9
EPD_CS/1.4C: J1.12
EPD_DC/1.5D: J1.11
EPD_RST/1.5D: J1.10
GDR: J1.2, Q3.1 (G), R2_EP_DR.2
GND: C1-EP-DR.2, C27.1, C29.1, C30.1, C31.1, C32.1, C34.1, C42.2, C43.2, D3.2 (GND), D4.1 (K), EPD_C1.1, EPD_C2.1, EPD_C5.1, EPD_C6.1, EPD_C7.1, EPD_C8.1, EPD_C9.1, EPD_C10.1, EPD_C11.1, EPD_C12.1, IC2.B1 (IN/TRIG), IC2.B3 (GND), J1.8, J1.17, J1.MP1, J1.MP2, J4.A1_B12 (GND), J4.A12_B1 (GND), J4.SH1 (SHIELD), J4.SH2 (SHIELD), J4.SH3 (SHIELD), J4.SH4 (SHIELD), R1_USB.1, R2_EP_DR.1, R2_USB.2, R_TYPE_SEL.1, SJ1.1, SW_DN.1, SW_ENT.1, SW_UP.1, TP_BAT_GND.TP, U3.1 (CTG), U3.4 (GND), U3.6 (QSTRT), U3.9 (EP); also elsewhere on the board
HAPTIC_EN/1.4C: IC2.A1 (EN)
MOSI/1.5B: J1.14
unnamed: C32.2, IC2.A2 (REG)
unnamed: C2-EP-DR.2, D5.2 (A), L5.2, Q3.3 (D)
unnamed: C2-EP-DR.1, D2.1 (K), D4.2 (A)
unnamed: EPD_C10.2, J1.22
unnamed: EPD_C2.2, J1.4
unnamed: EPD_C1.2, J1.5
unnamed: R1_EP_DR.1, R_TYPE_SEL.2, SJ1.2
unnamed: J4.B5 (CC2), R2_USB.1
unnamed: J4.A5 (CC1), R1_USB.2
unnamed: EPD_C6.2, J1.18
unnamed: EPD_C7.2, J1.19
unnamed: EPD_C8.2, J1.20
unnamed: EPD_C12.2, J1.24
OUT+: IC2.A3 (OUT+), TP_OP.TP
OUT-: IC2.C3 (OUT-), TP_ON.TP
P0.13/1.5D: C30.2, R5.1, SW_UP.2
P0.14/1.5D: C31.2, R8.1, SW_ENT.2
P1.01/1.6C: DMG2305UX-7.1 (G), R_PWR_EPD.1
P1.02/1.6C: C29.2, R7.1, SW_DN.2
PREVGH: D5.1 (K), EPD_C9.2, J1.21
PREVGL: D2.2 (A), EPD_C11.2, J1.23
RESE: J1.3, Q3.2 (S), R1_EP_DR.2
SCK/1.5B: J1.13
SCL/1.4C: IC2.C1 (SCL), U3.7 (SCL)
SDA/1.4C: IC2.B2 (SDA), U3.8 (SDA)
VBAT/1.2A: C27.2, TP_VBAT.TP, U3.2 (CELL), U3.3 (VDD)
VBUS/1.5D: C42.1, C43.1, D3.5 (VBUS), J4.A4_B9 (VBUS), J4.A9_B4 (VBUS)

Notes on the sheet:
E-Paper Drive Circuit
E-Paper Display Connector
Haptic Driver
Fuel Gauge
Buttons
USB C Connector & ESD Protection

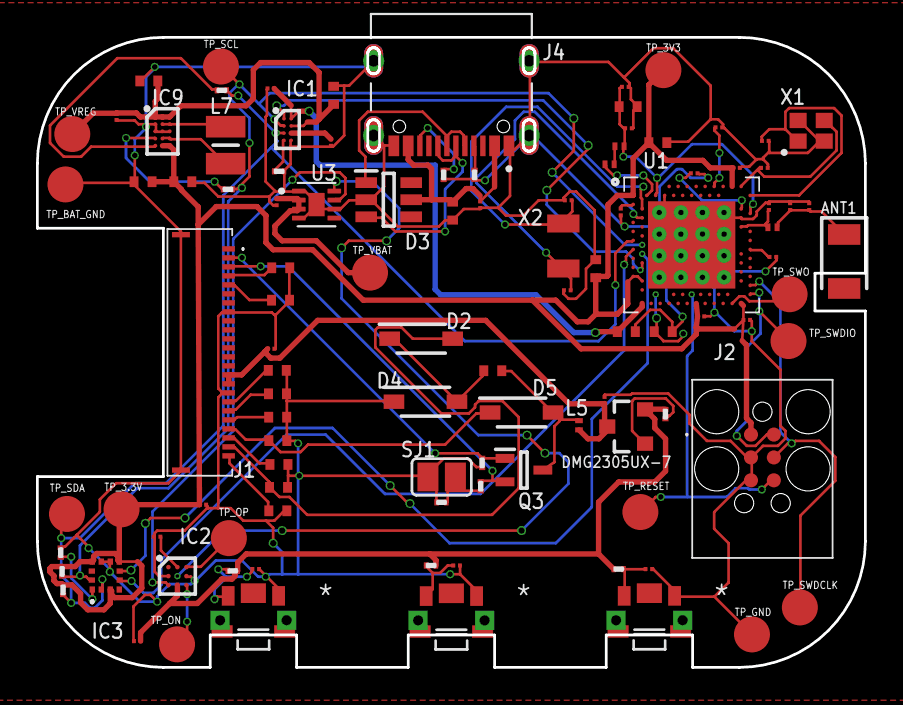
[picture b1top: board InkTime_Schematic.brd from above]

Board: 2 copper layers, 46.0 x 35.0 mm, 105 parts (0 on the bottom side), 65 nets.

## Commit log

2026-04-19 final

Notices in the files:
parts and their libraries:
COPYRIGHT: Copyright (C) 2025 Ultra Librarian. All rights reserved.
